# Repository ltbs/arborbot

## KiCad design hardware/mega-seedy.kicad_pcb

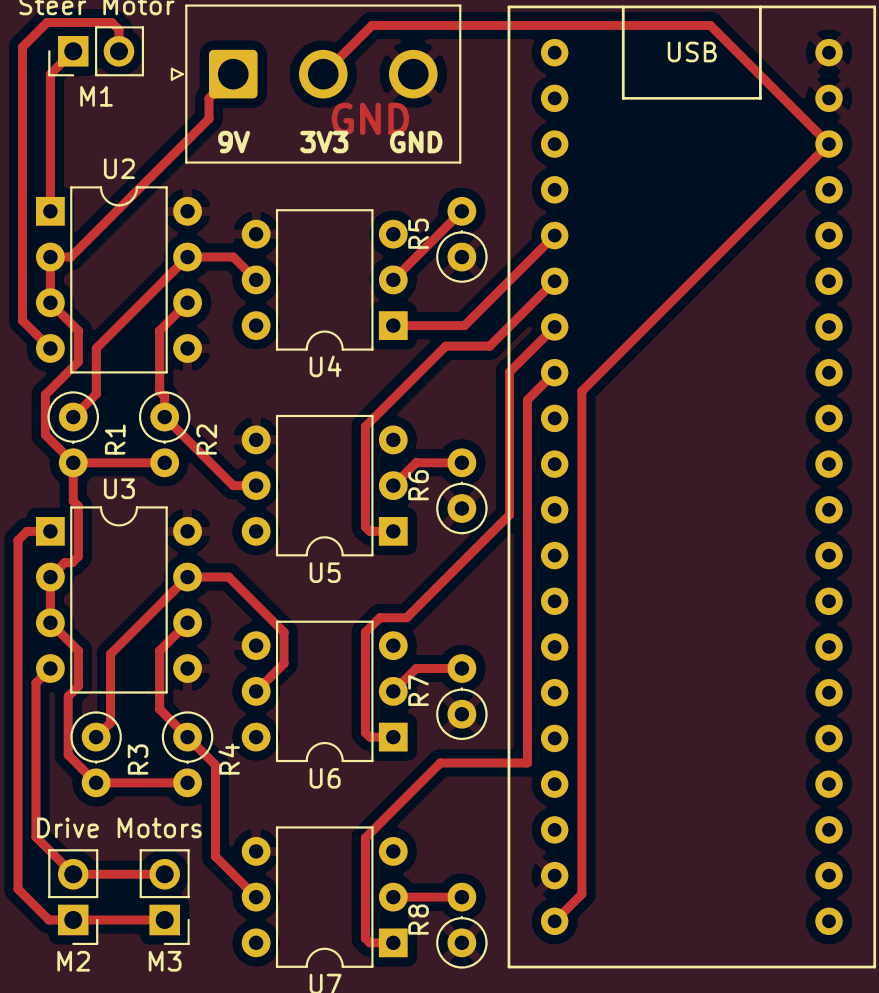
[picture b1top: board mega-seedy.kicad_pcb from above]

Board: 2 copper layers, 19 parts (0 on the bottom side), 19 nets.

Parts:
J1: Conn_01x03_Male; JST_NV_B03P-NV_1x03_P5.00mm_Vertical
M1: Steer Motor; PinHeader_1x02_P2.54mm_Vertical
M2: Drive Motors; PinHeader_1x02_P2.54mm_Vertical
M3: Back Mtr; PinHeader_1x02_P2.54mm_Vertical
R1, R2, R3, R4: 2k2; R_Axial_DIN0207_L6.3mm_D2.5mm_P2.54mm_Vertical
R5, R6, R7, R8: 200; R_Axial_DIN0207_L6.3mm_D2.5mm_P2.54mm_Vertical
U1: ChinaBluePill
U2, U3: L9110; DIP-8_W7.62mm
U4, U5, U6, U7: 4N25; DIP-6_W7.62mm

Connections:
+3V3: J1.2, U1.3V3
+9V: J1.1, R1.2, R2.2, R3.2, R4.2, U2.2, U2.3, U3.2, U3.3
GND: J1.3, R5.1, R6.1, R7.1, R8.1, U1.GND, U2.5, U2.8, U3.5, U3.8, U4.4, U5.4, U6.4, U7.4
unnamed: M1.1, U2.1
unnamed: M1.2, U2.4
unnamed: M2.1, M3.1, U3.1
unnamed: M2.2, M3.2, U3.4
unnamed: R1.1, U2.7, U4.5
unnamed: R2.1, U2.6, U5.5
unnamed: R3.1, U3.7, U6.5
unnamed: R4.1, U3.6, U7.5
unnamed: R5.2, U4.2
unnamed: R6.2, U5.2
unnamed: R7.2, U6.2
unnamed: R8.2, U7.2
unnamed: U1.PA8, U4.1
unnamed: U1.PA9, U5.1
unnamed: U1.PA10, U6.1
unnamed: U1.PA11, U7.1

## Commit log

2019-11-23 Create LICENSE
2019-11-23 add low production volume schematic
2019-12-22 schematic updated for sensor arrays, comms, etc
